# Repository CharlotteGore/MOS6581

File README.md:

# MOS6581

C++(ish) library for controlling a MOS 6581/8580 via SPI on Arduino. Rather than requiring a MIDI in signal, this library is about putting direct and full control of the SID's 24 writeable registers into the programmer's hands in a fairly friendly API.

Also included in this repo is the schematic and board files for the PCB I've had made to interface with SID chips. It only deals with talking to the SID and getting output out without damaging it - handling MIDI-in or some other system of control is left to you. 

I've recently refactored this library to have a less fluent API but certaintly a more practical one in terms of integrating into embedded systems.

## Basics

This library programs the SID via the hardware SPI on an Arduino, and uses pin 2 as the SID chip select and pin 3 as the shift register latch. The library shunts data at the shift registers least significant bit first, so Q7 connects to A0, Q3 to A5, Q7 to D0 and Q0 to D7 etc. It sends the address data first, then the data so the data line from the SPI connects to the 'data' shift register, and the Q7' to the data in on the 'address' shift register. 

It assumes an external 1mhz crystal oscillator instead of trying to use an internal one. There's code in the library, commented out, which will turn pin 9 on an Uno/Nano into a 1mhz clock pin. Help yourself.

The following code is about the minimum required to get a SID to make a noise - any noise. Set the volume, set an envelope, set a waveform and turn a channel on, and set a frequency. This software makes that trivial. 

```c++
MOS6581 sid;

void setup(){

    sid = MOS6581();
    // or if you need to change pin assignments...
    // sid = MOS6581(SHIFT_REG_LATCH_PIN, SID_CHIP_SELECT_PIN, SID_CLOCK_PIN)

   sid.reset();
   sid.volume(15); // set volume to the maximum, 15.

   sid.setMode(0, SID_RAMP); //set voice 0 to a ramp waveform
   sid.setADEnvelope(0,0,0); //Set voice 0's Attack and Decay envelope
   sid.setSREnvelope(0,15,0); //Set voice 0's Sustain and Release envelope
   sid.setFrequency(0, 1600); //Set voice 0's frequency
  
   sid.setVoice(0,1); Set voice 0 to 'on'.

}
```

## Using/Compiling

I've only been able to get this library to work with the Visual Studio Arduino plugin. It doesn't seem to work with the official Arduino IDE. It's possible I've just missed something simple - haven't done C++ or an Arduino library before.

UPDATE: It **does** work with the standard Arduino IDE. The name of the folder must match the name of the files exactly.. that solved it!

## API

## Global Controls

### .reset()

Populates all the registers with 0.

### .volume(byte vol)

Set the global output volume. 0 - 15. 

## Individual voice controls

A number between 0 and 15 to set the master output volume.

### .setMode(byte voice, byte mode)

Select a waveform for a voice. Options are SID_SQUARE, SID_RAMP, SID_TRIANGLE, SID_TEST, SID_RING, SID_SYNC. You can use binary maths to select multiple waveform generators but this isn't recommended.

### .setFrequency(byte voice, byte mode)

Set a frequency for a voice. Frequency is a 16bit number, 0-65535. TO DO: Lookup for real notes->frequency. 

### .setPulseWidth(byte voice, word frequency)

Set a frequency for the Square wave duty cycle. No effect unless SID_SQUARE is selected as a voice's mode. Frequency is a 12 bit number, 0-4095.

### .setADEnvelope(byte voice, byte attack, byte decay)
### .setSREnvelope(byte voice, byte sustain, byte release)

Set the amplitude modulation envelope of a voice. Now split into two seperate functions. Each parameter is a number between 0-15. 

To simply play and hold a note, indefinitely, the correct setting is 0,0,15,0.

### .setVoice(byte voice, boolean on)

Turn a voice on or off. Without a valid frequency, waveform and envelope this might not do anythign noticable.  

### .setFilter(byte voice, boolean on)

Set a voice to either go or not go through the filter.

## Filter Controls

### .setFilterMode(byte mode)

Set the filter's mode. Valid options are SID_FILT_LP, SID_FILT_HP, SID_FILT_LP and SID_FILT_OFF (which mutes any voices going through it) you can logical OR them together, i.e, ```SID_FILT_LP | SID_FILT_HP``` to create a notch filter.  

### .filterFrequency(word frequency)

Set the filter cutoff frequency. This is a 10 bit number, 0 - 1023

### .filterResonance(byte resonance)

Set the resonance amount. This is a 4 bit number, 0-15.

## Just in Case

### .transfer(byte address, byte value)

Write whatever you want directly to a SID register, if you know what you're doing. Generally the API exposes everything except the read-only registers so perhaps this might be useful for that. 

## Project updates and things

Current setup: SID/Arduino Interface board with another breadboard with an Arduino Nano, MIDI in circuit, a 1mhz Oscillator and two 4051 demux chips for handling all the analog inputs on the control surface.

Here's the ridiculous hot pink control surface I made. It doesn't quite have enough controls. I need at least 2 more toggle switches... whoops. 

This was the first working breadboard I set up - just enough to control a SID with pure code and output a sound.

Here's a friend playing on the SID. It demonstrates multiple voices being used, along with the filter.
[Sound sample](https://github.com/CharlotteGore/MOS6581/raw/master/multi-voice-random.mp3)

Some of the first noises I got out of a SID. This one was a complete mess. 
[Sound sample](https://github.com/CharlotteGore/MOS6581/raw/master/sid-test.mp3)

## DISCLAIMER OF DOOM

Copyright (c) 2013 Charlotte Gore

Permission is hereby granted, free of charge, to any person obtaining a copy
of this software and associated documentation files (the "Software"), to deal
in the Software without restriction, including without limitation the rights
to use, copy, modify, merge, publish, distribute, sublicense, and/or sell
copies of the Software, and to permit persons to whom the Software is
furnished to do so, subject to the following conditions:

The above copyright notice and this permission notice shall be included in
all copies or substantial portions of the Software.

THE SOFTWARE IS PROVIDED "AS IS", WITHOUT WARRANTY OF ANY KIND, EXPRESS OR IMPLIED, INCLUDING BUT NOT LIMITED TO THE WARRANTIES OF MERCHANTABILITY, FITNESS FOR A PARTICULAR PURPOSE AND NONINFRINGEMENT. IN NO EVENT SHALL THE
AUTHORS OR COPYRIGHT HOLDERS BE LIABLE FOR ANY CLAIM, DAMAGES OR OTHER LIABILITY, WHETHER IN AN ACTION OF CONTRACT, TORT OR OTHERWISE, ARISING FROM, OUT OF OR IN CONNECTION WITH THE SOFTWARE OR THE USE OR OTHER DEALINGS IN THE SOFTWARE.

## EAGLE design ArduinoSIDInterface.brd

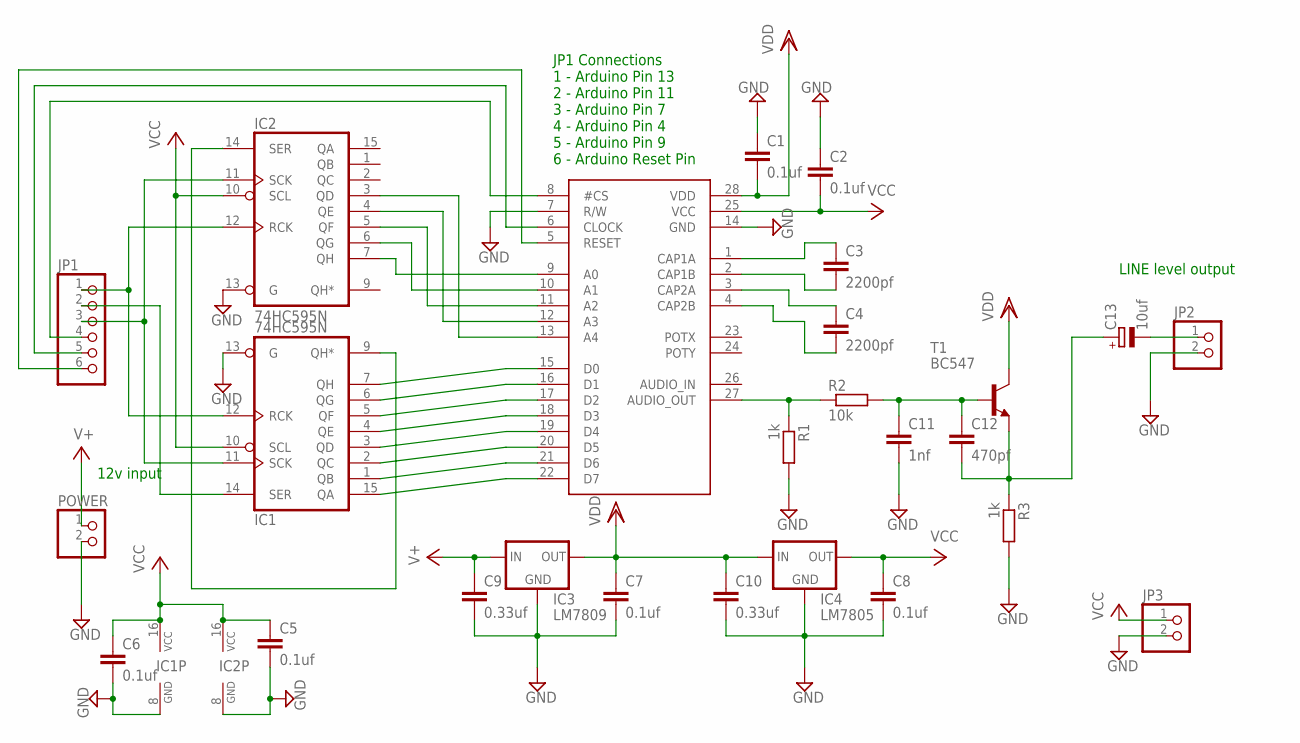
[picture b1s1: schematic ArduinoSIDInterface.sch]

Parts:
C1: 0.1uf; C050-035X075
C2, C5, C6: 0.1uf; C050-030X075
C3, C4: 2200pf; C075-042X103
C7, C8: 0.1uf; C10B4
C9, C10: 0.33uf; C15B5
C11: 1nf; C050-030X075
C12: 470pf; C050-030X075
C13: 10uf; E2-5
IC1, IC2: 74HC595N; DIL16
IC3: LM7809; 78XXS
IC4: LM7805; 78XXS
JP1: PINHD-1X6; 1X06
JP2, JP3: PINHD-1X2; 1X02
POWER: PINHD-1X2; 1X02
R1, R3: 1k; 0204/7
R2: 10k; 0204/7
T1: BC547; TO92
U$1: 6581; DIL28-6

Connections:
D0: IC1.7 (QH), U$1.15 (D0)
D1: IC1.6 (QG), U$1.16 (D1)
D2: IC1.5 (QF), U$1.17 (D2)
D3: IC1.4 (QE), U$1.18 (D3)
D4: IC1.3 (QD), U$1.19 (D4)
D5: IC1.2 (QC), U$1.20 (D5)
D6: IC1.1 (QB), U$1.21 (D6)
D7: IC1.15 (QA), U$1.22 (D7)
DATA: JP1.4, U$1.8 (#CS)
GND: C1.1, C2.1, C5.2, C6.2, C7.2, C8.2, C9.2, C10.2, C11.2, IC1.8 (GND), IC1.13 (G), IC2.8 (GND), IC2.13 (G), IC3.GND, IC4.GND, JP2.2, JP3.2, POWER.2, R1.2, R3.2, U$1.7 (R/W), U$1.14 (GND)
unnamed: IC1.9 (QH*), IC2.14 (SER)
unnamed: C3.1, U$1.1 (CAP1A)
unnamed: IC2.7 (QH), U$1.9 (A0)
unnamed: IC2.6 (QG), U$1.10 (A1)
unnamed: IC2.5 (QF), U$1.11 (A2)
unnamed: IC2.4 (QE), U$1.12 (A3)
unnamed: IC2.3 (QD), U$1.13 (A4)
unnamed: JP1.5, U$1.6 (CLOCK)
unnamed: JP1.6, U$1.5 (RESET)
unnamed: C3.2, U$1.2 (CAP1B)
unnamed: C4.1, U$1.3 (CAP2A)
unnamed: C4.2, U$1.4 (CAP2B)
unnamed: R1.1, R2.1, U$1.27 (AUDIO_OUT)
unnamed: C11.1, C12.1, R2.2, T1.2 (B)
unnamed: C12.2, C13.+, R3.1, T1.1 (E)
unnamed: C13.-, JP2.1
RCK: IC1.12 (RCK), IC2.12 (RCK), JP1.1
SCK: IC1.11 (SCK), IC2.11 (SCK), JP1.3
SER: IC1.14 (SER), JP1.2
V+: C9.1, IC3.IN, POWER.1
VCC: C2.2, C5.1, C6.1, C8.1, IC1.10 (SCL), IC1.16 (VCC), IC2.10 (SCL), IC2.16 (VCC), IC4.OUT, JP3.1, U$1.25 (VCC)
VDD: C1.2, C7.1, C10.1, IC3.OUT, IC4.IN, T1.3 (C), U$1.28 (VDD)

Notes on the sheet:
JP1 Connections 1 - Arduino Pin 13 2 - Arduino Pin 11 3 - Arduino Pin 7 4 - Arduino Pin 4 5 - Arduino Pin 9 6 - Arduino Reset Pin
12v input
LINE level output

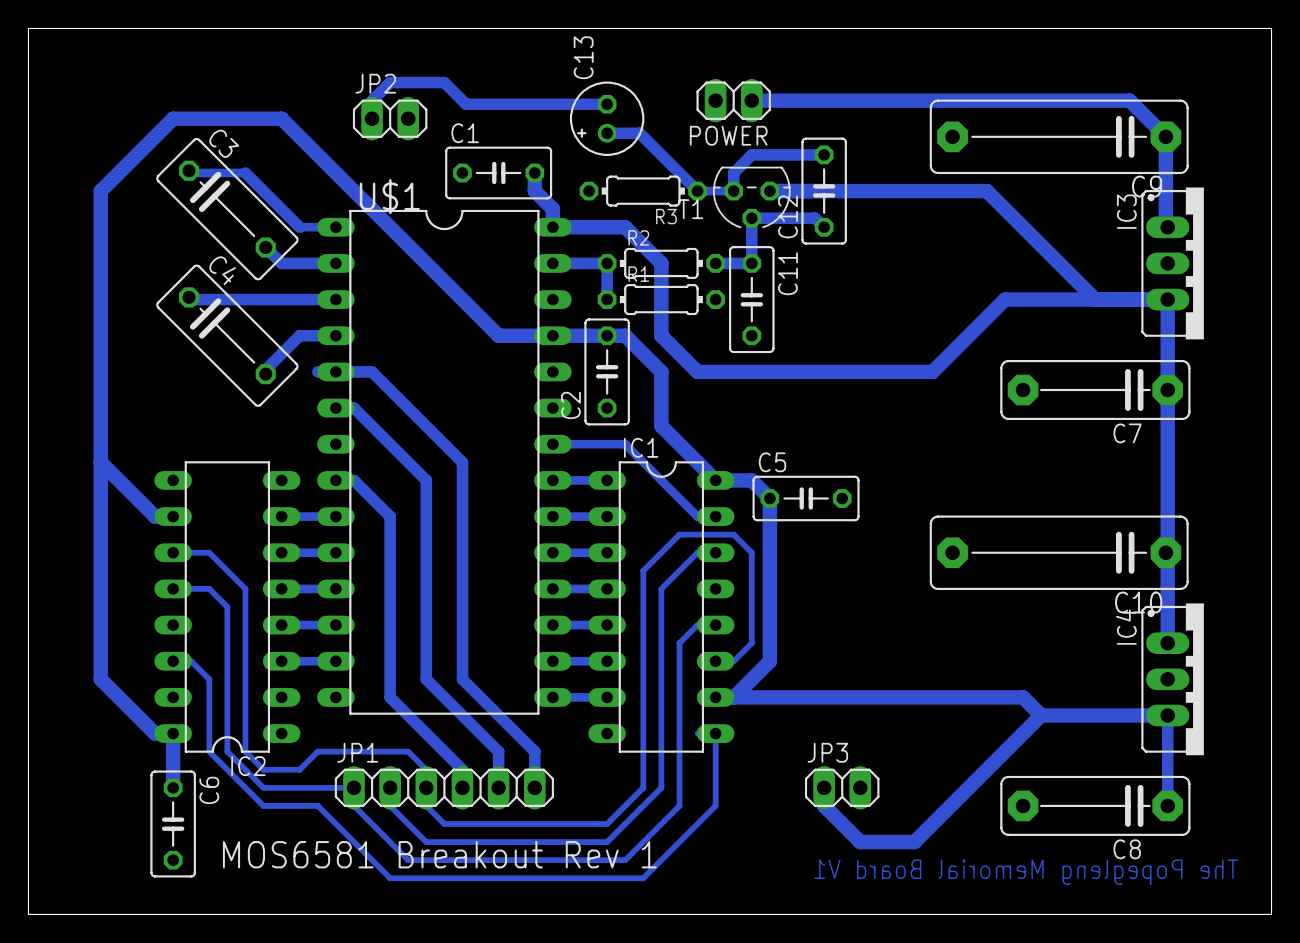
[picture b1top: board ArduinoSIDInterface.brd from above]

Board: 2 copper layers, 87.3 x 62.2 mm, 26 parts (0 on the bottom side), 32 nets.

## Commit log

2013-06-01 Initial Commit of SID library
2013-06-01 Added template doc
2013-06-02 Added Voice On/Off. Changed some timings for experimenting. Removed debug command
2013-06-02 Added schematic
2013-06-02 Added Eagle source files as well. Why the hell not!
2013-06-02 Added audio sample and a picture of the first breadboard prototype
2013-06-03 Revised the schematic and board layout. Shift register->SID connections now inverted so Q7->D0 and Q0->D7. Requires a change to the SPI initialisation to be compatible but the board layout is a lot n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
2013-06-05 Updated some packages on the schematic and slightly rearranged the board.
2013-06-05 Fixup schematic
2013-06-05 Increased trace widths
2013-06-05 Fixed up trace thickness, ground plane distance etc
2013-06-05 More tweaks to the board
2013-06-17 Added latest pictures, code and samples.
2013-06-21 Updated code to be compatible with PCB
